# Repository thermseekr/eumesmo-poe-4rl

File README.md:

# eumesmo-poe-4rl
PoE powered ESP32 based board featuring 4 SPST NO relays. Ideal for access control, doors, isolated zones or for installing anywhere you need to click dry contacts near some equipment or appliance.

## VERSION HISTORY

V1.1 - 2026/07/02 - Added CPU health LED.

V1.0 - 2026/06/16 - Initial release.

## LICENSE

This project is licensed under the [Creative Commons BY-NC 4.0 License](https://creativecommons.org/licenses/by-nc/4.0/).
Commercial use is not permitted without prior written consent. See the [LICENSE.txt](LICENSE.txt) file for details.

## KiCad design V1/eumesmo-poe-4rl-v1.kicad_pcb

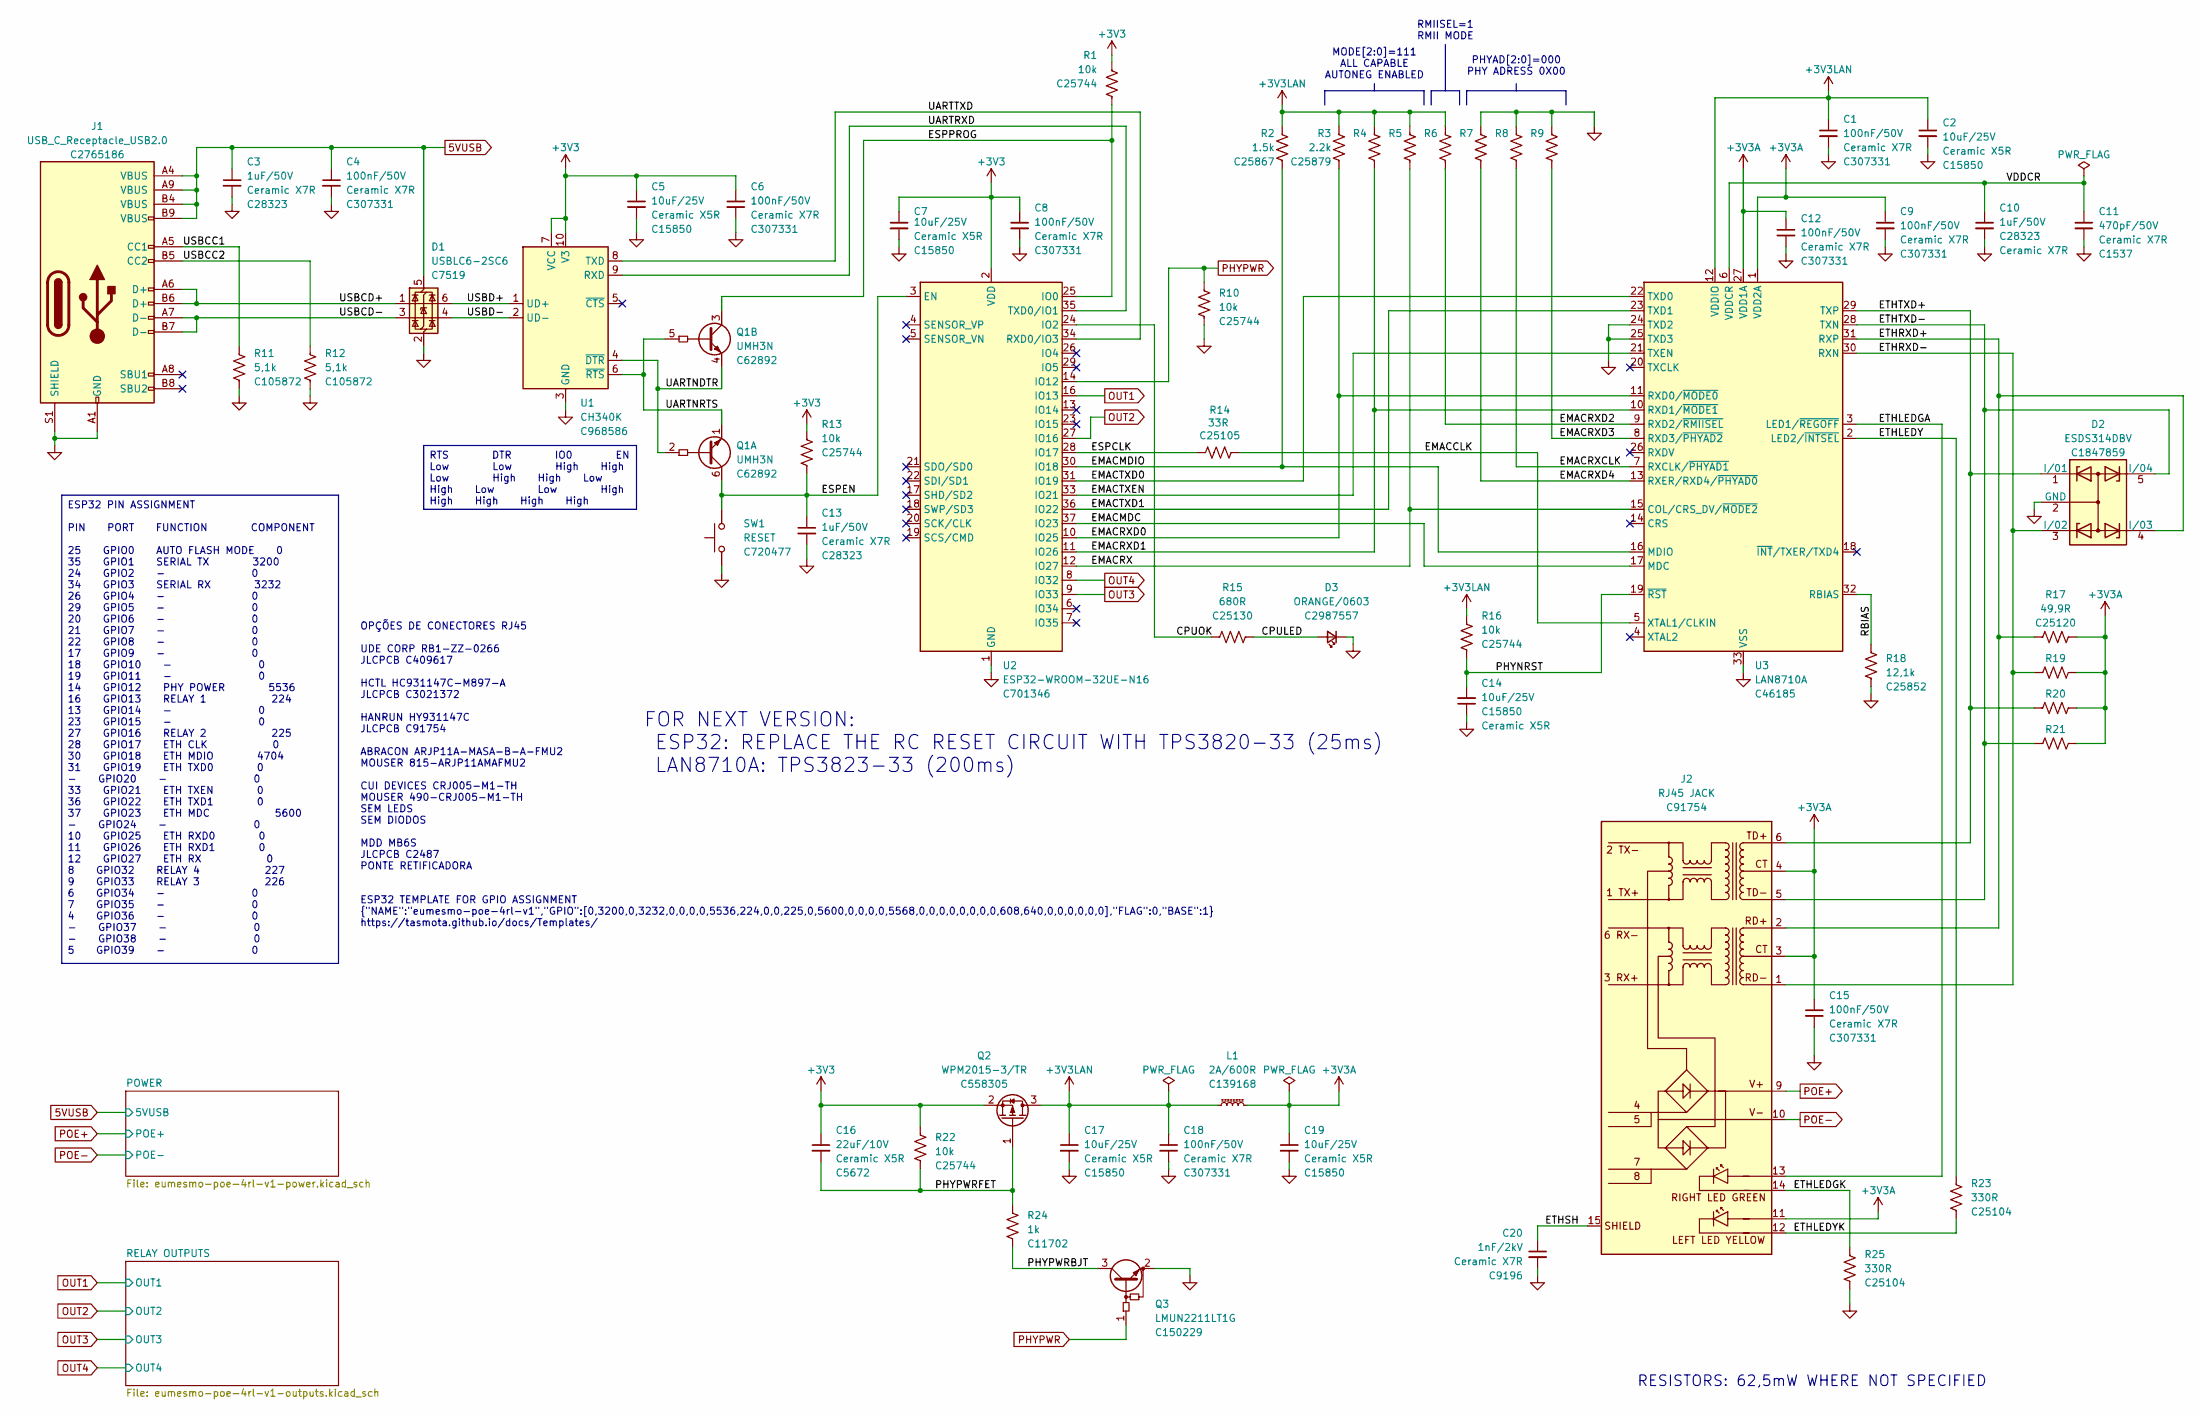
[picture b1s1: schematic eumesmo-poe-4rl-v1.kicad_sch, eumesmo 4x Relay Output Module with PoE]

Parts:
C1, C4, C6, C8, C9, C12, C15, C18: 100nF/50V; C_0402_1005Metric; Mfr PN CL05B104KB54PNC; JLCPCB BOM 1
C2, C7, C14, C17, C19: 10uF/25V; C_0805_2012Metric; Mfr PN CL21A106KAYNNNE; JLCPCB BOM 1
C3, C10, C13: 1uF/50V; C_0805_2012Metric; Mfr PN CL21B105KBFNNNE; JLCPCB BOM 1
C5: 10uF/25V; C_0805_2012Metric; Mfr PN CL21A106KAYNNNE; LCSC Part # C15850
C11: 470pF/50V; C_0402_1005Metric; Mfr PN 0402B471K500NT; JLCPCB BOM 1
C16: 22uF/10V; C_1206_3216Metric; Mfr PN CL31A226KPHNNNE; JLCPCB BOM 1
C20: 1nF/2kV; C_1206_3216Metric; Mfr PN 1206B102K202NT; JLCPCB BOM 1
D1: USBLC6-2SC6; SOT-23-6; Mfr PN USBLC6-2SC6; JLCPCB BOM 1
D2: ESDS314DBV; SOT-23-5; Mfr PN ESDS314DBVR; JLCPCB BOM 1
D3: ORANGE/0603; LED_0603_1608Metric; Mfr PN 19-217/S2C-AL1M2VY/6T; LCSC Part # C2987557
J1: USB_C_Receptacle_USB2.0; USB_C_Receptacle_GCT_USB4105-xx-A_16P_TopMnt_Horizontal; Mfr PN TYPE-C 16PIN 2MD(073); JLCPCB BOM 1
J2: RJ45 JACK; RJ45_HanRun_HY931147C; Mfr PN HY931147C; JLCPCB BOM 1
L1: 2A/600R; L_0805_2012Metric; Mfr PN CBM201209U601T; JLCPCB BOM 1
Q1: UMH3N; SOT-363_SC-70-6; Mfr PN UMH3N; JLCPCB BOM 1
Q2: WPM2015-3/TR; SOT-23; Mfr PN WPM2015-3/TR; JLCPCB BOM 1
Q3: LMUN2211LT1G; SOT-23; Mfr PN MMUN2211LT3G; LCSC Part # C150229
R1, R10, R13, R16, R22: 10k; R_0402_1005Metric; Mfr PN 0402WGF1002TCE; LCSC Part # C25744
R2: 1.5k; R_0402_1005Metric; Mfr PN 0402WGF1501TCE; LCSC Part # C25867
R3, R4, R5, R6, R7, R8, R9: 2.2k; R_0402_1005Metric; Mfr PN 0402WGF2201TCE; LCSC Part # C25879
R11, R12: 5,1k; R_0402_1005Metric; Mfr PN RC0402FR-075K1L; JLCPCB BOM 1
R14: 33R; R_0402_1005Metric; Mfr PN 0402WGF330JTCE; JLCPCB BOM 1
R15: 680R; R_0402_1005Metric; Mfr PN 0402WGF6800TCE; LCSC Part # C25130
R17, R19, R20, R21: 49,9R; R_0402_1005Metric; Mfr PN 0402WGF499JTCE; JLCPCB BOM 1
R18: 12,1k; R_0402_1005Metric; Mfr PN 0402WGF1212TCE; JLCPCB BOM 1
R23, R25: 330R; R_0402_1005Metric; Mfr PN 0402WGF3300TCE; LCSC Part # C25104
R24: 1k; R_0402_1005Metric; Mfr PN 0402WGF1001TCE; LCSC Part # C11702
SW1: RESET; SW_SPST_Xunpu_TS1088AR02016; Mfr PN TS-1088-AR02016; JLCPCB BOM 1
U1: CH340K; SSOP-10-1EP_3.9x4.9mm_P1mm_EP2.1x3.3mm; Mfr PN CH340K; JLCPCB BOM 1
U2: ESP32-WROOM-32UE-N16; ESP32-WROOM-32U; Mfr PN ESP32-WROOM-32UE-N16; JLCPCB BOM 1
U3: LAN8710A; QFN-32-1EP_5x5mm_P0.5mm_EP3.3x3.3mm_ThermalVias; Mfr PN LAN8710A-EZC-TR; JLCPCB BOM 1

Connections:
5VUSB: C3.1, C4.1, D1.5 (VBUS), J1.A4 (VBUS), J1.A9 (VBUS), J1.B4 (VBUS), J1.B9 (VBUS); also elsewhere on the board
+3V3: C5.1, C6.1, C7.1, C8.1, C16.1, Q2.2 (S), R1.1, R13.1, R22.1, U1.7 (VCC), U1.10 (V3), U2.2 (VDD); also elsewhere on the board
+3V3A: C9.1, C12.1, C15.1, C19.1, J2.3 (CT), J2.4 (CT), J2.11 (LLED+), L1.2, R17.2, R19.2, R20.2, R21.2, U3.1 (VDD2A), U3.27 (VDD1A)
+3V3LAN: C1.1, C2.1, C17.1, C18.1, L1.1, Q2.3 (D), R2.1, R3.1, R4.1, R5.1, R6.1, R16.2, U3.12 (VDDIO)
/CPULED: D3.2 (A), R15.2
/CPUOK: R15.1, U2.24 (IO2)
/EMACCLK: R14.2, U3.5 (XTAL1/CLKIN)
/EMACMDC: U2.37 (IO23), U3.17 (MDC)
/EMACMDIO: R2.2, U2.30 (IO18), U3.16 (MDIO)
/EMACRX: R5.2, U2.12 (IO27), U3.15 (COL/CRS_DV/~MODE2)
/EMACRXCLK: R8.2, U3.7 (RXCLK/~PHYAD1)
/EMACRXD0: R3.2, U2.10 (IO25), U3.11 (RXD0/~MODE0)
/EMACRXD1: R4.2, U2.11 (IO26), U3.10 (RXD1/~MODE1)
/EMACRXD2: R6.2, U3.9 (RXD2/~RMIISEL)
/EMACRXD3: R9.2, U3.8 (RXD3/~PHYAD2)
/EMACRXD4: R7.2, U3.13 (RXER/RXD4/~PHYAD0)
/EMACTXD0: U2.31 (IO19), U3.22 (TXD0)
/EMACTXD1: U2.36 (IO22), U3.23 (TXD1)
/EMACTXEN: U2.33 (IO21), U3.21 (TXEN)
/ESPCLK: R14.1, U2.28 (IO17)
/ESPEN: C13.1, Q1.6 (C1), R13.2, SW1.2, U2.3 (EN)
/ESPPROG: Q1.3 (C2), R1.2, U2.25 (IO0)
/ETHLEDGA: J2.13 (RLED+), U3.3 (LED1/~REGOFF)
/ETHLEDGK: J2.14 (RLED-), R25.2
/ETHLEDY: R23.2, U3.2 (LED2/~INTSEL)
/ETHLEDYK: J2.12 (LLED-), R23.1
/ETHRXD+: D2.4 (I/03), J2.2 (RD+), R17.1, U3.31 (RXP)
/ETHRXD-: D2.3 (I/02), J2.1 (RD-), R19.1, U3.30 (RXN)
/ETHSH: C20.1, J2.15 (SHIELD)
/ETHTXD+: D2.1 (I/01), J2.6 (TD+), R20.1, U3.29 (TXP)
/ETHTXD-: D2.5 (I/04), J2.5 (TD-), R21.1, U3.28 (TXN)
/PHYNRST: C14.2, R16.1, U3.19 (~RST)
/PHYPWRBJT: Q3.3 (C), R24.2
/PHYPWRFET: C16.2, Q2.1 (G), R22.2, R24.1
/RBIAS: R18.1, U3.32 (RBIAS)
/UARTNDTR: Q1.2 (B1), Q1.4 (E2), U1.4 (~DTR)
/UARTNRTS: Q1.1 (E1), Q1.5 (B2), U1.6 (~RTS)
/UARTRXD: U1.9 (RXD), U2.35 (TXD0/IO1)
/UARTTXD: U1.8 (TXD), U2.34 (RXD0/IO3)
/USBCC1: J1.A5 (CC1), R11.1
/USBCC2: J1.B5 (CC2), R12.1
/USBCD+: D1.1 (I/O1), J1.A6 (D+), J1.B6 (D+)
/USBCD-: D1.3 (I/O2), J1.A7 (D-), J1.B7 (D-)
/USBD+: D1.6 (I/O1), U1.1 (UD+)
/USBD-: D1.4 (I/O2), U1.2 (UD-)
/VDDCR: C10.1, C11.1, U3.6 (VDDCR)
GND: C1.2, C2.2, C3.2, C4.2, C5.2, C6.2, C7.2, C8.2, C9.2, C10.2, C11.2, C12.2, C13.2, C14.1, C15.2, C17.2, C18.2, C19.2, C20.2, D1.2 (GND), D2.2 (GND), D3.1 (K), J1.A1 (GND), J1.A12 (GND), J1.B1 (GND), J1.B12 (GND), J1.S1 (SHIELD), Q3.2 (E), R7.1, R8.1, R9.1, R10.1, R11.2, R12.2, R18.2, R25.1, SW1.1, U1.3 (GND), U1.11 (GND), U2.1 (GND), U2.15 (GND), U2.38 (GND), U2.39 (GND), U3.24 (TXD2), U3.25 (TXD3), U3.33 (VSS); also elsewhere on the board
OUT1: U2.16 (IO13); also elsewhere on the board
OUT2: U2.27 (IO16); also elsewhere on the board
OUT3: U2.9 (IO33); also elsewhere on the board
OUT4: U2.8 (IO32); also elsewhere on the board
PHYPWR: Q3.1 (B), R10.2, U2.14 (IO12)
POE+: J2.9 (V+); also elsewhere on the board
POE-: J2.10 (V-); also elsewhere on the board

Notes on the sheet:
RMIISEL=1 RMII MODE
PHYAD[2:0]=000 PHY ADRESS 0X00
OPÇÕES DE CONECTORES RJ45 UDE CORP RB1-ZZ-0266 JLCPCB C409617 HCTL HC931147C-M897-A JLCPCB C3021372 HANRUN HY931147C JLCPCB C91754 ABRACON ARJP11A-MASA-B-A-FMU2 MOUSER 815-ARJP11AMAFMU2 CUI DEVICES CRJ005-M1-TH MOUSER 490-CRJ005-M1-TH SEM LEDS SEM DIODOS MDD MB6S JLCPCB C2487 PONTE RETIFICADORA
ESP32 TEMPLATE FOR GPIO ASSIGNMENT {"NAME":"eumesmo-poe-4rl-v1","GPIO":[0,3200,0,3232,0,0,0,0,5536,224,0,0,225,0,5600,0,0,0,0,5568,0,0,0,0,0,0,0,0,608,640,0,0,0,0,0,0],"FLAG":0,"BASE":1} https://tasmota.github.io/docs/Templates/
RESISTORS: 62,5mW WHERE NOT SPECIFIED
MODE[2:0]=111 ALL CAPABLE AUTONEG ENABLED
FOR NEXT VERSION: ESP32: REPLACE THE RC RESET CIRCUIT WITH TPS3820-33 (25ms) LAN8710A: TPS3823-33 (200ms)
ESP32 PIN ASSIGNMENT PIN PORT FUNCTION COMPONENT 25 GPIO0 AUTO FLASH MODE 0 35 GPIO1 SERIAL TX 3200 24 GPIO2 - 0 34 GPIO3 SERIAL RX 3232 26 GPIO4 - 0 29 GPIO5 - 0 20 GPIO6 - 0 21 GPIO7 - 0 22 GPIO8 - 0 17 GPIO9 - 0 18 GPIO10 - 0 19 GPIO11 - 0 14 GPIO12 PHY POWER 5536 16 GPIO13 RELAY 1 224 13 GPIO14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
RTS DTR IO0 EN Low Low High High Low High High Low High Low Low High High High High High

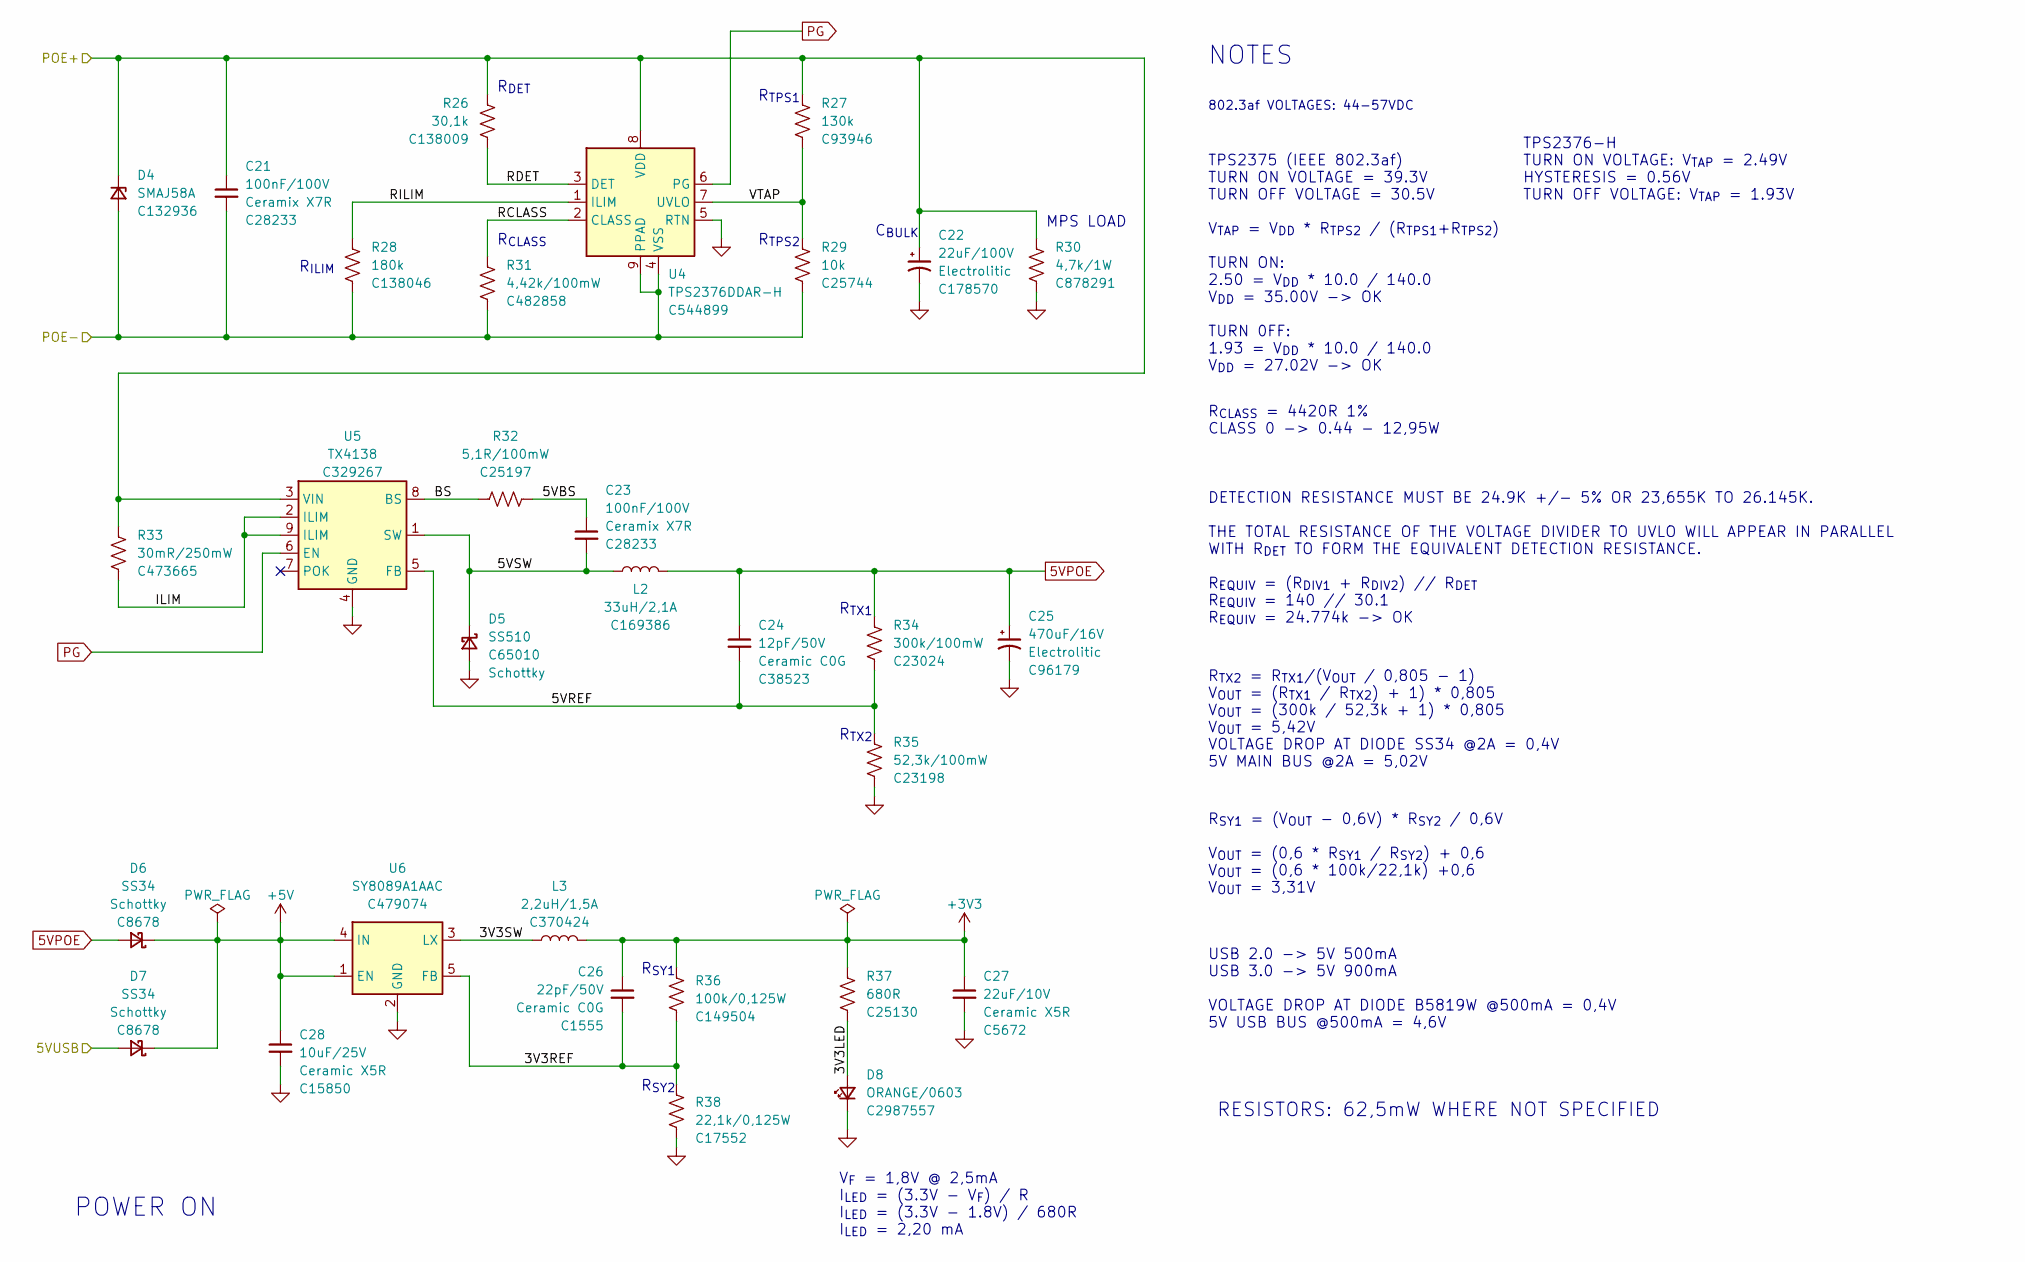
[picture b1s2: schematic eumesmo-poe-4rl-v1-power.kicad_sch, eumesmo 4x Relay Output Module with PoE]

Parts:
C21: 100nF/100V; C_0805_2012Metric; Mfr PN CL21B104KCFNNNE; JLCPCB BOM 1
C22: 22uF/100V; CP_Elec_8x10.5; Mfr PN EEEFK2A220P; LCSC Part # C178570
C23: 100nF/100V; C_0805_2012Metric; Mfr PN CL21B104KCFNNNE; LCSC Part # C28233
C24: 12pF/50V; C_0603_1608Metric; Mfr PN CL10C120JB8NNNC; JLCPCB BOM 1
C25: 470uF/16V; CP_Elec_8x10.5; Mfr PN CS1C471M-CRF10; JLCPCB BOM 1
C26: 22pF/50V; C_0402_1005Metric; Mfr PN 0402CG220J500NT; JLCPCB BOM 1
C27: 22uF/10V; C_1206_3216Metric; Mfr PN CL31A226KPHNNNE; JLCPCB BOM 1
C28: 10uF/25V; C_0805_2012Metric; Mfr PN CL21A106KAYNNNE; JLCPCB BOM 1
D4: SMAJ58A; D_SMA; Mfr PN SMAJ58A-TR; JLCPCB BOM 1
D5: SS510; D_SMA; Mfr PN SS510; JLCPCB BOM 1
D6, D7: SS34; D_SMA; Mfr PN SS34; JLCPCB BOM 1
D8: ORANGE/0603; LED_0603_1608Metric; Mfr PN 19-217/S2C-AL1M2VY/6T; LCSC Part # C2987557
L2: 33uH/2,1A; L_12x12mm_H6mm; Mfr PN SWRB1205S-330MT; JLCPCB BOM 1
L3: 2,2uH/1,5A; L_3x3mm_H1.5mm; Mfr PN SPH3015H2R2MT; JLCPCB BOM 1
R26: 30,1k; R_0402_1005Metric; Mfr PN RC0402FR-0730K1L; JLCPCB BOM 1
R27: 130k; R_0402_1005Metric; Mfr PN RC0402FR-07130KL; JLCPCB BOM 1
R28: 180k; R_0402_1005Metric; Mfr PN RC0402FR-07180KL; JLCPCB BOM 1
R29: 10k; R_0402_1005Metric; Mfr PN 0402WGF1002TCE; JLCPCB BOM 1
R30: 4,7k/1W; R_2512_6332Metric; Mfr PN RC2512JK-074K7L; JLCPCB BOM 1
R31: 4,42k/100mW; R_0603_1608Metric; Mfr PN RC0603FR-074K42L; JLCPCB BOM 1
R32: 5,1R/100mW; R_0603_1608Metric; Mfr PN 0603WAF510KT5E; LCSC Part # C25197
R33: 30mR/250mW; R_1206_3216Metric; Mfr PN 1206W3F300MT5E; LCSC Part # C473665
R34: 300k/100mW; R_0603_1608Metric; Mfr PN 0603WAF3003T5E; JLCPCB BOM 1
R35: 52,3k/100mW; R_0603_1608Metric; Mfr PN 0603WAF5232T5E; JLCPCB BOM 1
R36: 100k/0,125W; R_0805_2012Metric; Mfr PN 0805W8F1003T5E; JLCPCB BOM 1
R37: 680R; R_0402_1005Metric; Mfr PN 0402WGF6800TCE; LCSC Part # C25130
R38: 22,1k/0,125W; R_0805_2012Metric; Mfr PN 0805W8F2212T5E; JLCPCB BOM 1
U4: TPS2376DDAR-H; SOIC-8-1EP_3.9x4.9mm_P1.27mm_EP2.95x4.9mm_Mask2.71x3.4mm_Th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; Mfr PN TPS2376DDAR-H; JLCPCB BOM 1
U5: TX4138; SOIC-8-1EP_3.9x4.9mm_P1.27mm_EP2.41x3.81mm_ThermalVias; Mfr PN TX4138; JLCPCB BOM 1
U6: SY8089A1AAC; SOT-23-5_Shorter_Pins; Mfr PN SY8089A1AAC; JLCPCB BOM 1

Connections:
5VPOE: C24.1, C25.1, D6.2 (A), L2.2, R34.1
5VUSB: D7.2 (A); also elsewhere on the board
+3V3: C26.1, C27.1, L3.2, R36.1, R37.1; also elsewhere on the board
+5V: C28.1, D6.1 (K), D7.1 (K), U6.1 (EN), U6.4 (IN); also elsewhere on the board
/POWER/3V3LED: D8.2 (A), R37.2
/POWER/3V3REF: C26.2, R36.2, R38.1, U6.5 (FB)
/POWER/3V3SW: L3.1, U6.3 (LX)
/POWER/5VBS: C23.1, R32.1
/POWER/5VREF: C24.2, R34.2, R35.1, U5.5 (FB)
/POWER/5VSW: C23.2, D5.1 (K), L2.1, U5.1 (SW)
/POWER/BS: R32.2, U5.8 (BS)
/POWER/ILIM: R33.2, U5.2 (ILIM), U5.9 (ILIM)
/POWER/RCLASS: R31.1, U4.2 (CLASS)
/POWER/RDET: R26.2, U4.3 (DET)
/POWER/RILIM: R28.1, U4.1 (ILIM)
/POWER/VTAP: R27.2, R29.1, U4.7 (UVLO)
GND: C22.2, C25.2, C27.2, C28.2, D5.2 (A), D8.1 (K), R30.2, R35.2, R38.2, U4.5 (RTN), U5.4 (GND), U6.2 (GND); also elsewhere on the board
PG: U4.6 (PG), U5.6 (EN)
POE+: C21.1, C22.1, D4.1 (K), R26.1, R27.1, R30.1, R33.1, U4.8 (VDD), U5.3 (VIN); also elsewhere on the board
POE-: C21.2, D4.2 (A), R28.2, R29.2, R31.2, U4.4 (VSS), U4.9 (PPAD); also elsewhere on the board

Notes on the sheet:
R_{TPS1}
R_{TX2}
DETECTION RESISTANCE MUST BE 24.9K +/- 5% OR 23,655K TO 26.145K. THE TOTAL RESISTANCE OF THE VOLTAGE DIVIDER TO UVLO WILL APPEAR IN PARALLEL WITH R_{DET} TO FORM THE EQUIVALENT DETECTION RESISTANCE. R_{EQUIV} = (R_{DIV1} + R_{DIV2}) // R_{DET} R_{EQUIV} = 140 // 30.1 R_{EQUIV} = 24.774k -> OK
R_{SY2}
RESISTORS: 62,5mW WHERE NOT SPECIFIED
POWER ON
R_{CLASS} = 4420R 1% CLASS 0 -> 0.44 - 12,95W
R_{SY1}
R_{CLASS}
R_{TX2} = R_{TX1}/(V_{OUT} / 0,805 - 1) V_{OUT} = (R_{TX1} / R_{TX2}) + 1) * 0,805 V_{OUT} = (300k / 52,3k + 1) * 0,805 V_{OUT} = 5,42V VOLTAGE DROP AT DIODE SS34 @2A = 0,4V 5V MAIN BUS @2A = 5,02V
C_{BULK}
R_{ILIM}
USB 2.0 -> 5V 500mA USB 3.0 -> 5V 900mA VOLTAGE DROP AT DIODE B5819W @500mA = 0,4V 5V USB BUS @500mA = 4,6V
TPS2375 (IEEE 802.3af) TURN ON VOLTAGE = 39.3V TURN OFF VOLTAGE = 30.5V
TPS2376-H TURN ON VOLTAGE: V_{TAP} = 2.49V HYSTERESIS = 0.56V TURN OFF VOLTAGE: V_{TAP} = 1.93V
R_{SY1} = (V_{OUT} - 0,6V) * R_{SY2} / 0,6V V_{OUT} = (0,6 * R_{SY1} / R_{SY2}) + 0,6 V_{OUT} = (0,6 * 100k/22,1k) +0,6 V_{OUT} = 3,31V
R_{TPS2}
V_{F} = 1,8V @ 2,5mA I_{LED} = (3.3V - V_{F}) / R I_{LED} = (3.3V - 1.8V) / 680R I_{LED} = 2,20 mA
R_{TX1}
NOTES
MPS LOAD
R_{DET}
802.3af VOLTAGES: 44-57VDC
V_{TAP} = V_{DD} * R_{TPS2} / (R_{TPS1}+R_{TPS2}) TURN ON: 2.50 = V_{DD} * 10.0 / 140.0 V_{DD} = 35.00V -> OK TURN 0FF: 1.93 = V_{DD} * 10.0 / 140.0 V_{DD} = 27.02V -> OK

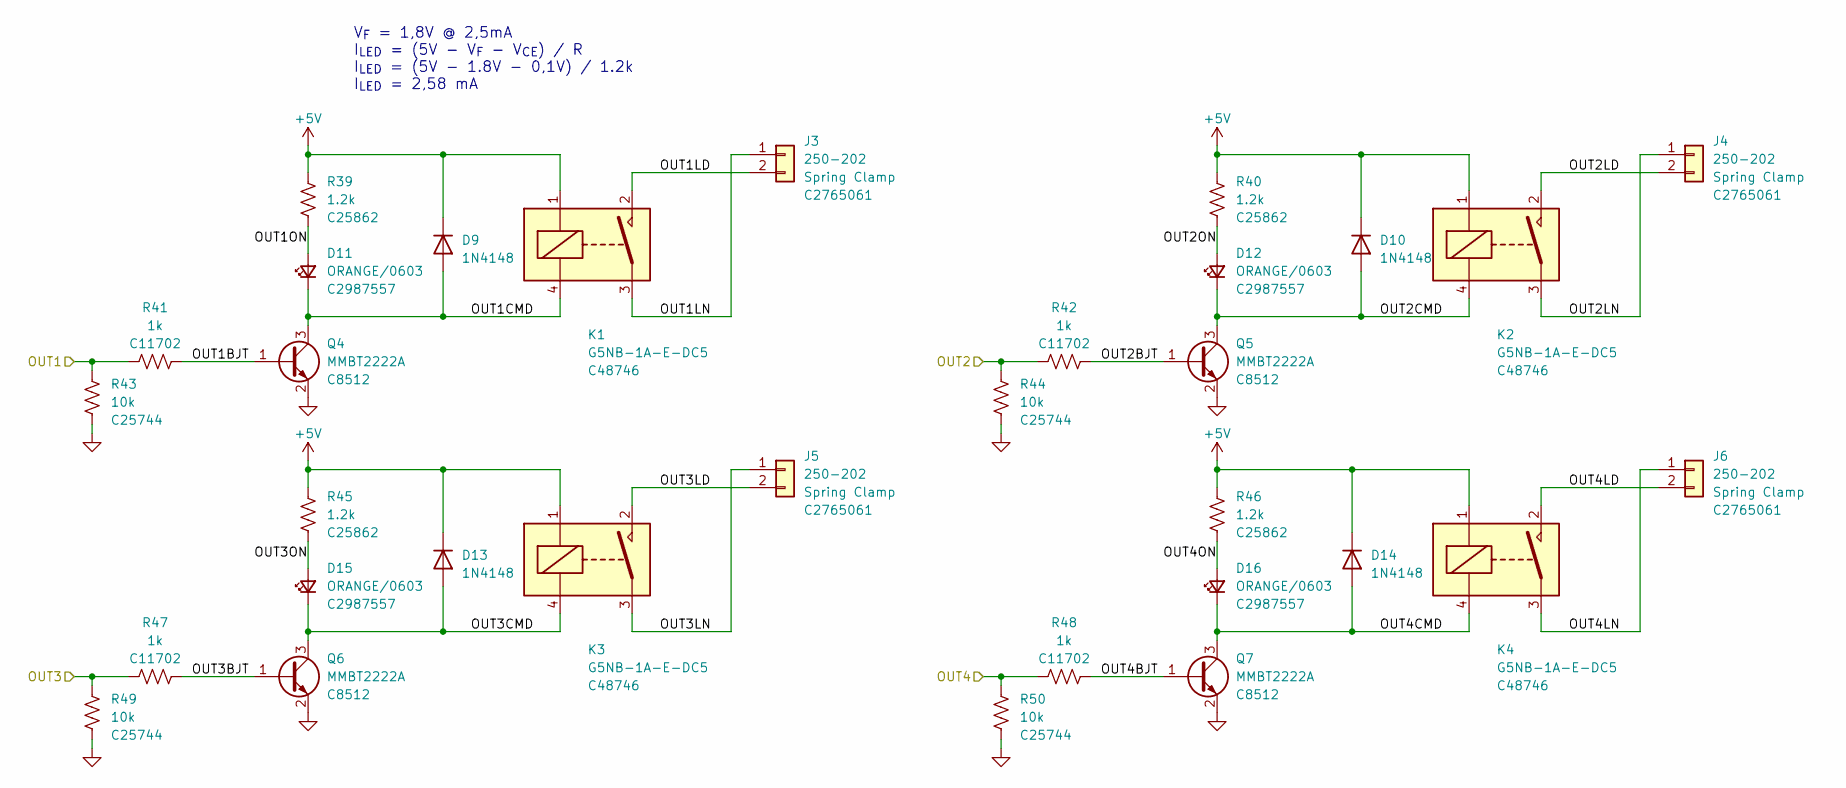
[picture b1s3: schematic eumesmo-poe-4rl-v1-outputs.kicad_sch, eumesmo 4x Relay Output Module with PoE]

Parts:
D9, D10, D13, D14: 1N4148; D_SOD-123; Mfr PN 1N4148W; JLCPCB BOM 1
D11, D12, D15, D16: ORANGE/0603; LED_0603_1608Metric; Mfr PN 19-217/S2C-AL1M2VY/6T; LCSC Part # C2987557
J3, J4, J5, J6: 250-202; TerminalBlock_Wago_250-202_1x02_P3.5mm_45Degree; Mfr PN 250-202; JLCPCB BOM 1
K1, K2, K3, K4: G5NB-1A-E-DC5; Relay_SPST_Omron_G5NB-1A; Mfr PN G5NB-1A-E-DC5; JLCPCB BOM 1
Q4, Q5, Q6, Q7: MMBT2222A; SOT-23; Mfr PN MMBT2222A; JLCPCB BOM 1
R39, R40, R45, R46: 1.2k; R_0402_1005Metric; Mfr PN 0402WGF1201TCE; LCSC Part # C25862
R41, R42, R47, R48: 1k; R_0402_1005Metric; Mfr PN 0402WGF1001TCE; LCSC Part # C11702
R43, R44, R49, R50: 10k; R_0402_1005Metric; Mfr PN 0402WGF1002TCE; LCSC Part # C25744

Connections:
+5V: D9.1 (K), D10.1 (K), D13.1 (K), D14.1 (K), K1.1, K2.1, K3.1, K4.1, R39.1, R40.1, R45.1, R46.1; also elsewhere on the board
/RELAY OUTPUTS/OUT1BJT: Q4.1 (B), R41.1
/RELAY OUTPUTS/OUT1CMD: D9.2 (A), D11.1 (K), K1.4, Q4.3 (C)
/RELAY OUTPUTS/OUT1LD: J3.2, K1.2
/RELAY OUTPUTS/OUT1LN: J3.1, K1.3
/RELAY OUTPUTS/OUT1ON: D11.2 (A), R39.2
/RELAY OUTPUTS/OUT2BJT: Q5.1 (B), R42.1
/RELAY OUTPUTS/OUT2CMD: D10.2 (A), D12.1 (K), K2.4, Q5.3 (C)
/RELAY OUTPUTS/OUT2LD: J4.2, K2.2
/RELAY OUTPUTS/OUT2LN: J4.1, K2.3
/RELAY OUTPUTS/OUT2ON: D12.2 (A), R40.2
/RELAY OUTPUTS/OUT3BJT: Q6.1 (B), R47.1
/RELAY OUTPUTS/OUT3CMD: D13.2 (A), D15.1 (K), K3.4, Q6.3 (C)
/RELAY OUTPUTS/OUT3LD: J5.2, K3.2
/RELAY OUTPUTS/OUT3LN: J5.1, K3.3
/RELAY OUTPUTS/OUT3ON: D15.2 (A), R45.2
/RELAY OUTPUTS/OUT4BJT: Q7.1 (B), R48.1
/RELAY OUTPUTS/OUT4CMD: D14.2 (A), D16.1 (K), K4.4, Q7.3 (C)
/RELAY OUTPUTS/OUT4LD: J6.2, K4.2
/RELAY OUTPUTS/OUT4LN: J6.1, K4.3
/RELAY OUTPUTS/OUT4ON: D16.2 (A), R46.2
GND: Q4.2 (E), Q5.2 (E), Q6.2 (E), Q7.2 (E), R43.2, R44.2, R49.2, R50.2; also elsewhere on the board
OUT1: R41.2, R43.1; also elsewhere on the board
OUT2: R42.2, R44.1; also elsewhere on the board
OUT3: R47.2, R49.1; also elsewhere on the board
OUT4: R48.2, R50.1; also elsewhere on the board

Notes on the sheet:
V_{F} = 1,8V @ 2,5mA I_{LED} = (5V - V_{F} - V_{CE}) / R I_{LED} = (5V - 1.8V - 0,1V) / 1.2k I_{LED} = 2,58 mA

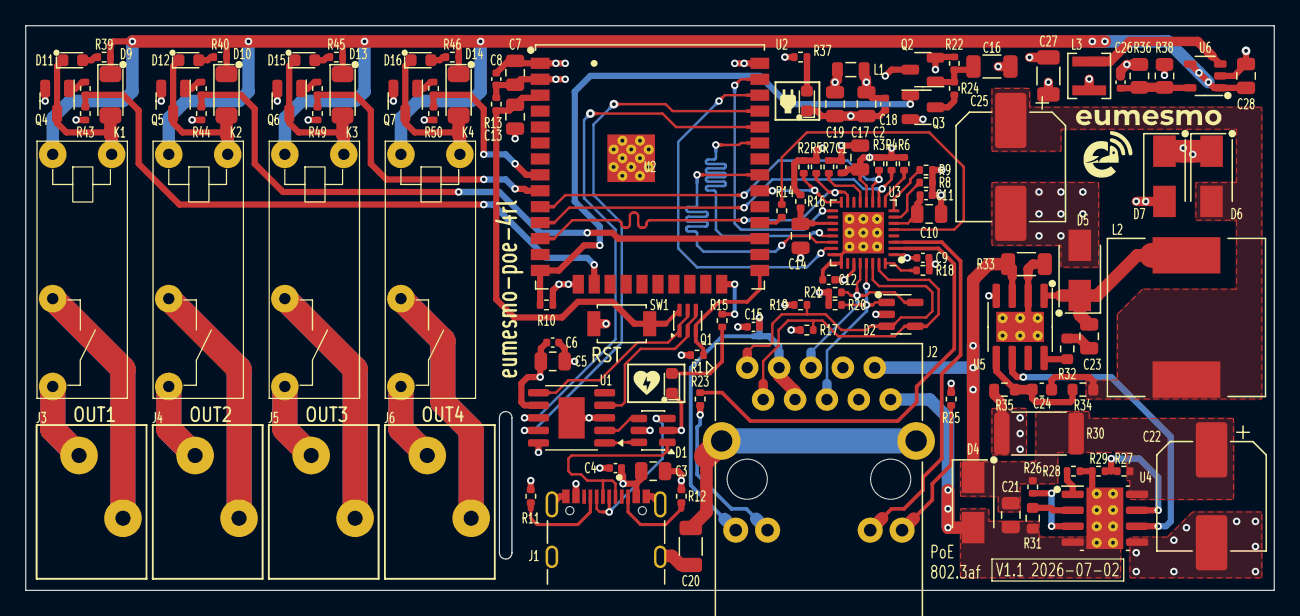
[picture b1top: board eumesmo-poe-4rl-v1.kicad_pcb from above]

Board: 4 copper layers, 99.5 x 45.0 mm, 121 parts (0 on the bottom side), 89 nets.

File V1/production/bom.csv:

Designator,Footprint,Quantity,Value,LCSC Part #
"C1, C12, C15, C18, C4, C6, C8, C9",0402,8,100nF/50V,C307331
"C10, C13, C3",0805,3,1uF/50V,C28323
C11,0402,1,470pF/50V,C1537
"C14, C17, C19, C2, C28, C5, C7",0805,7,10uF/25V,C15850
"C16, C27",1206,2,22uF/10V,C5672
C20,1206,1,1nF/2kV,C9196
"C21, C23",0805,2,100nF/100V,C28233
C22,CP_Elec_8x10.5,1,22uF/100V,C178570
C24,0603,1,12pF/50V,C38523
C25,CP_Elec_8x10.5,1,470uF/16V,C96179
C26,0402,1,22pF/50V,C1555
D1,SOT-23-6,1,USBLC6-2SC6,C7519
"D10, D13, D14, D9",D_SOD-123,4,1N4148,C81598
"D11, D12, D15, D16, D3, D8",0603,6,ORANGE/0603,C2987557
D2,SOT-23-5,1,ESDS314DBV,C1847859
D4,D_SMA,1,SMAJ58A,C132936
D5,D_SMA,1,SS510,C65010
"D6, D7",D_SMA,2,SS34,C8678
J1,USB_C_Receptacle_GCT_USB4105-xx-A_16P_TopMnt_Horizontal,1,USB_C_Receptacle_USB2.0,C2765186
J2,RJ45_HanRun_HY931147C,1,RJ45 JACK,C91754
"J3, J4, J5, J6",TerminalBlock_Wago_250-202_1x02_P3.5mm_45Degree,4,250-202,C2765061
"K1, K2, K3, K4",Relay_SPST_Omron_G5NB-1A,4,G5NB-1A-E-DC5,C48746
L1,0805,1,2A/600R,C139168
L2,L_12x12mm_H6mm,1,"33uH/2,1A",C169386
L3,L_3x3mm_H1.5mm,1,"2,2uH/1,5A",C370424
Q1,SOT-363_SC-70-6,1,UMH3N,C62892
Q2,SOT-23,1,WPM2015-3/TR,C558305
Q3,SOT-23,1,LMUN2211LT1G,C150229
"Q4, Q5, Q6, Q7",SOT-23,4,MMBT2222A,C8512
"R1, R10, R13, R16, R22, R29, R43, R44, R49, R50",0402,10,10k,C25744
"R11, R12",0402,2,"5,1k",C105872
R14,0402,1,33R,C25105
"R15, R37",0402,2,680R,C25130
"R17, R19, R20, R21",0402,4,"49,9R",C25120
R18,0402,1,"12,1k",C25852
R2,0402,1,1.5k,C25867
"R23, R25",0402,2,330R,C25104
"R24, R41, R42, R47, R48",0402,5,1k,C11702
R26,0402,1,"30,1k",C138009
R27,0402,1,130k,C93946
R28,0402,1,180k,C138046
"R3, R4, R5, R6, R7, R8, R9",0402,7,2.2k,C25879
R30,2512,1,"4,7k/1W",C878291
R31,0603,1,"4,42k/100mW",C482858
R32,0603,1,"5,1R/100mW",C25197
R33,1206,1,30mR/250mW,C473665
R34,0603,1,300k/100mW,C23024
R35,0603,1,"52,3k/100mW",C23198
R36,0805,1,"100k/0,125W",C149504
R38,0805,1,"22,1k/0,125W",C17552
"R39, R40, R45, R46",0402,4,1.2k,C25862
SW1,SW_SPST_Xunpu_TS1088AR02016,1,RESET,C720477
U1,SSOP-10-1EP_3.9x4.9mm_P1mm_EP2.1x3.3mm,1,CH340K,C968586
U2,ESP32-WROOM-32U,1,ESP32-WROOM-32UE-N16,C701346
U3,QFN-32-1EP_5x5mm_P0.5mm_EP3.3x3.3mm_ThermalVias,1,LAN8710A,C46185
U4,SOIC-8-1EP_3.9x4.9mm_P1.27mm_EP2.95x4.9mm_Mask2.71x3.4mm_ThermalVias,1,TPS2376DDAR-H,C544899
U5,SOIC-8-1EP_3.9x4.9mm_P1.27mm_EP2.41x3.81mm_ThermalVias,1,TX4138,C329267
U6,SOT-23-5_Shorter_Pins,1,SY8089A1AAC,C479074

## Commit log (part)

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2026-06-10 Update README with project details and licensing
    Added project description, version history, and license information.
2026-06-10 Upload gitignore and license
2026-06-10 Adapting the schematics from 2 to 4 outputs
2026-06-12 Under development.
2026-06-15 Development
2026-06-15 V1.0.0
2026-06-15 Adjusting traces width.
2026-06-16 Renamed all files to align with eumesmo branding.
2026-06-16 Rerouted TX/RX pairs between magjack and PHY.
2026-06-17 Widened pads at tracks and vias.
2026-06-17 Release V1.0.0
2026-06-30 Added CPU health LED
